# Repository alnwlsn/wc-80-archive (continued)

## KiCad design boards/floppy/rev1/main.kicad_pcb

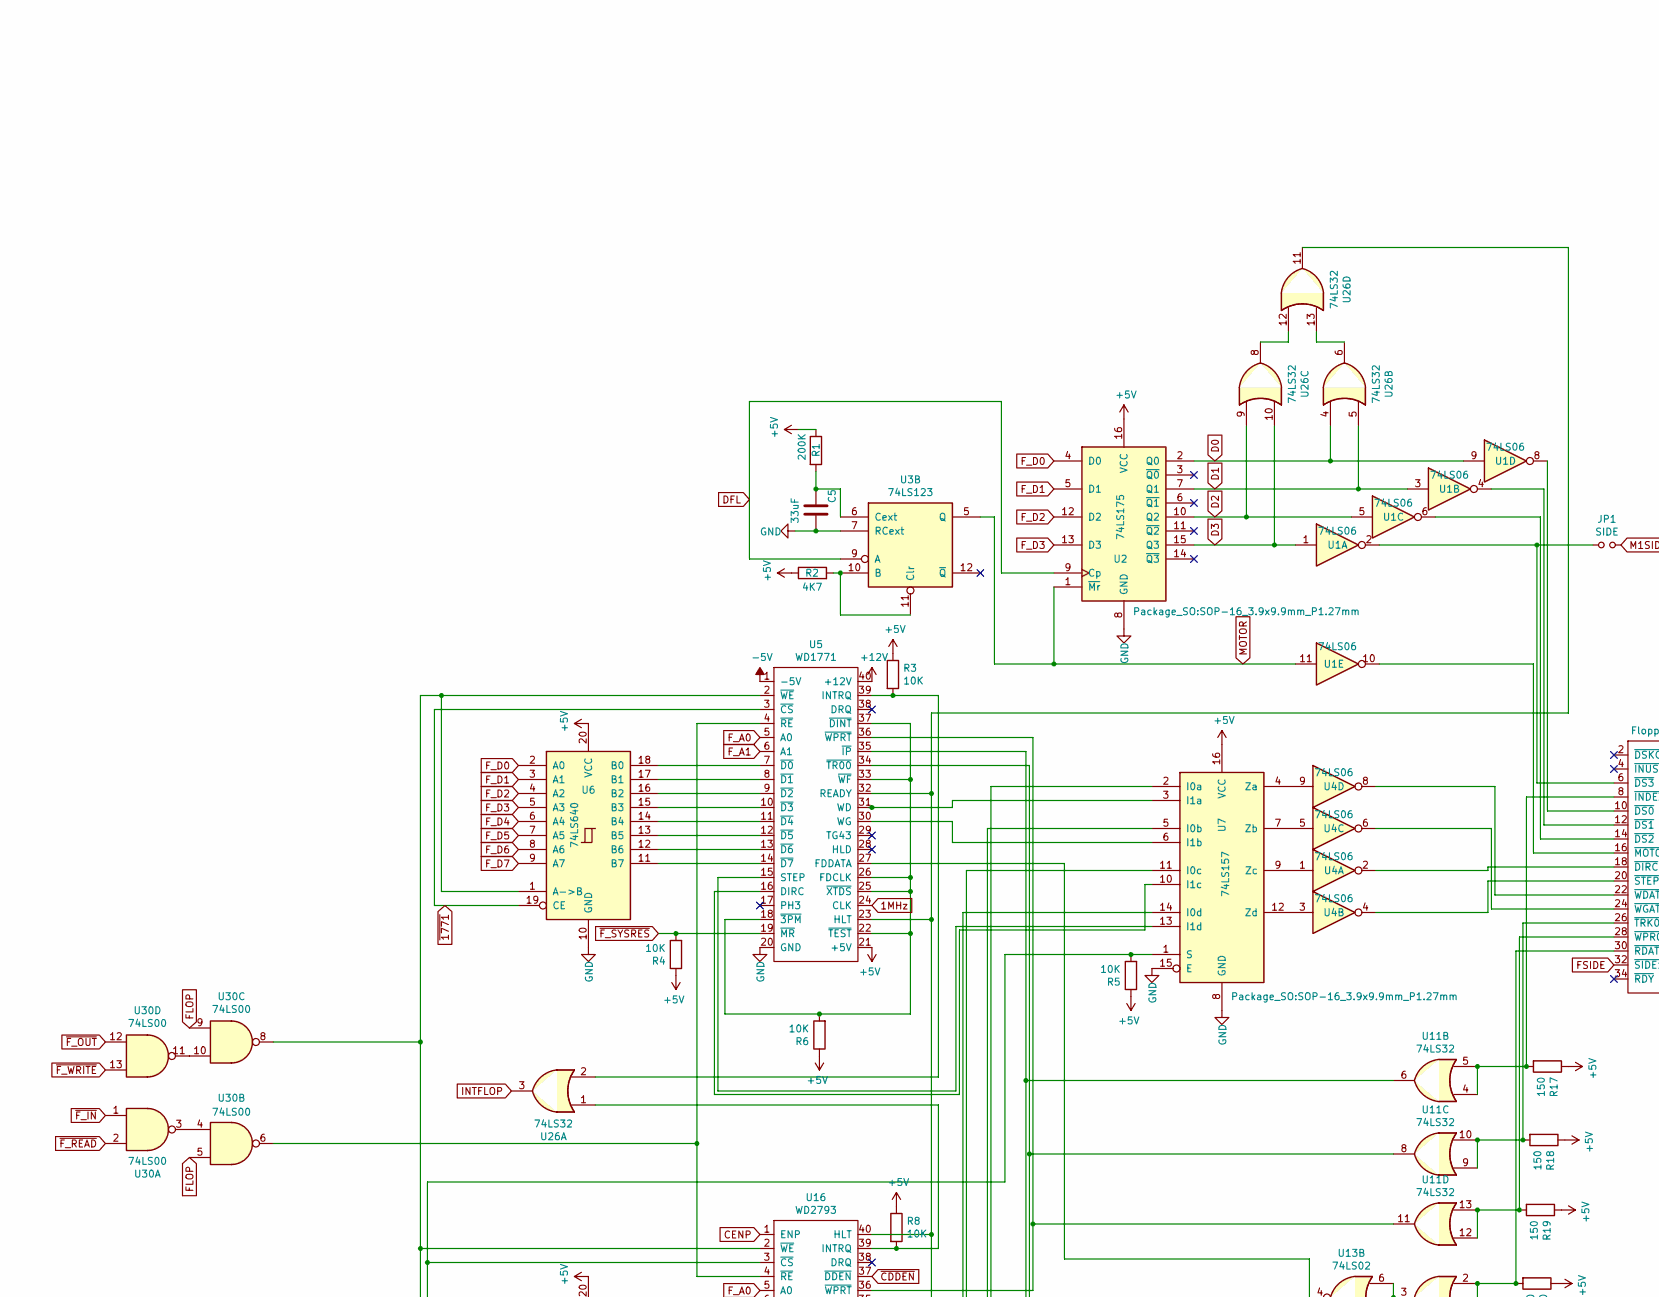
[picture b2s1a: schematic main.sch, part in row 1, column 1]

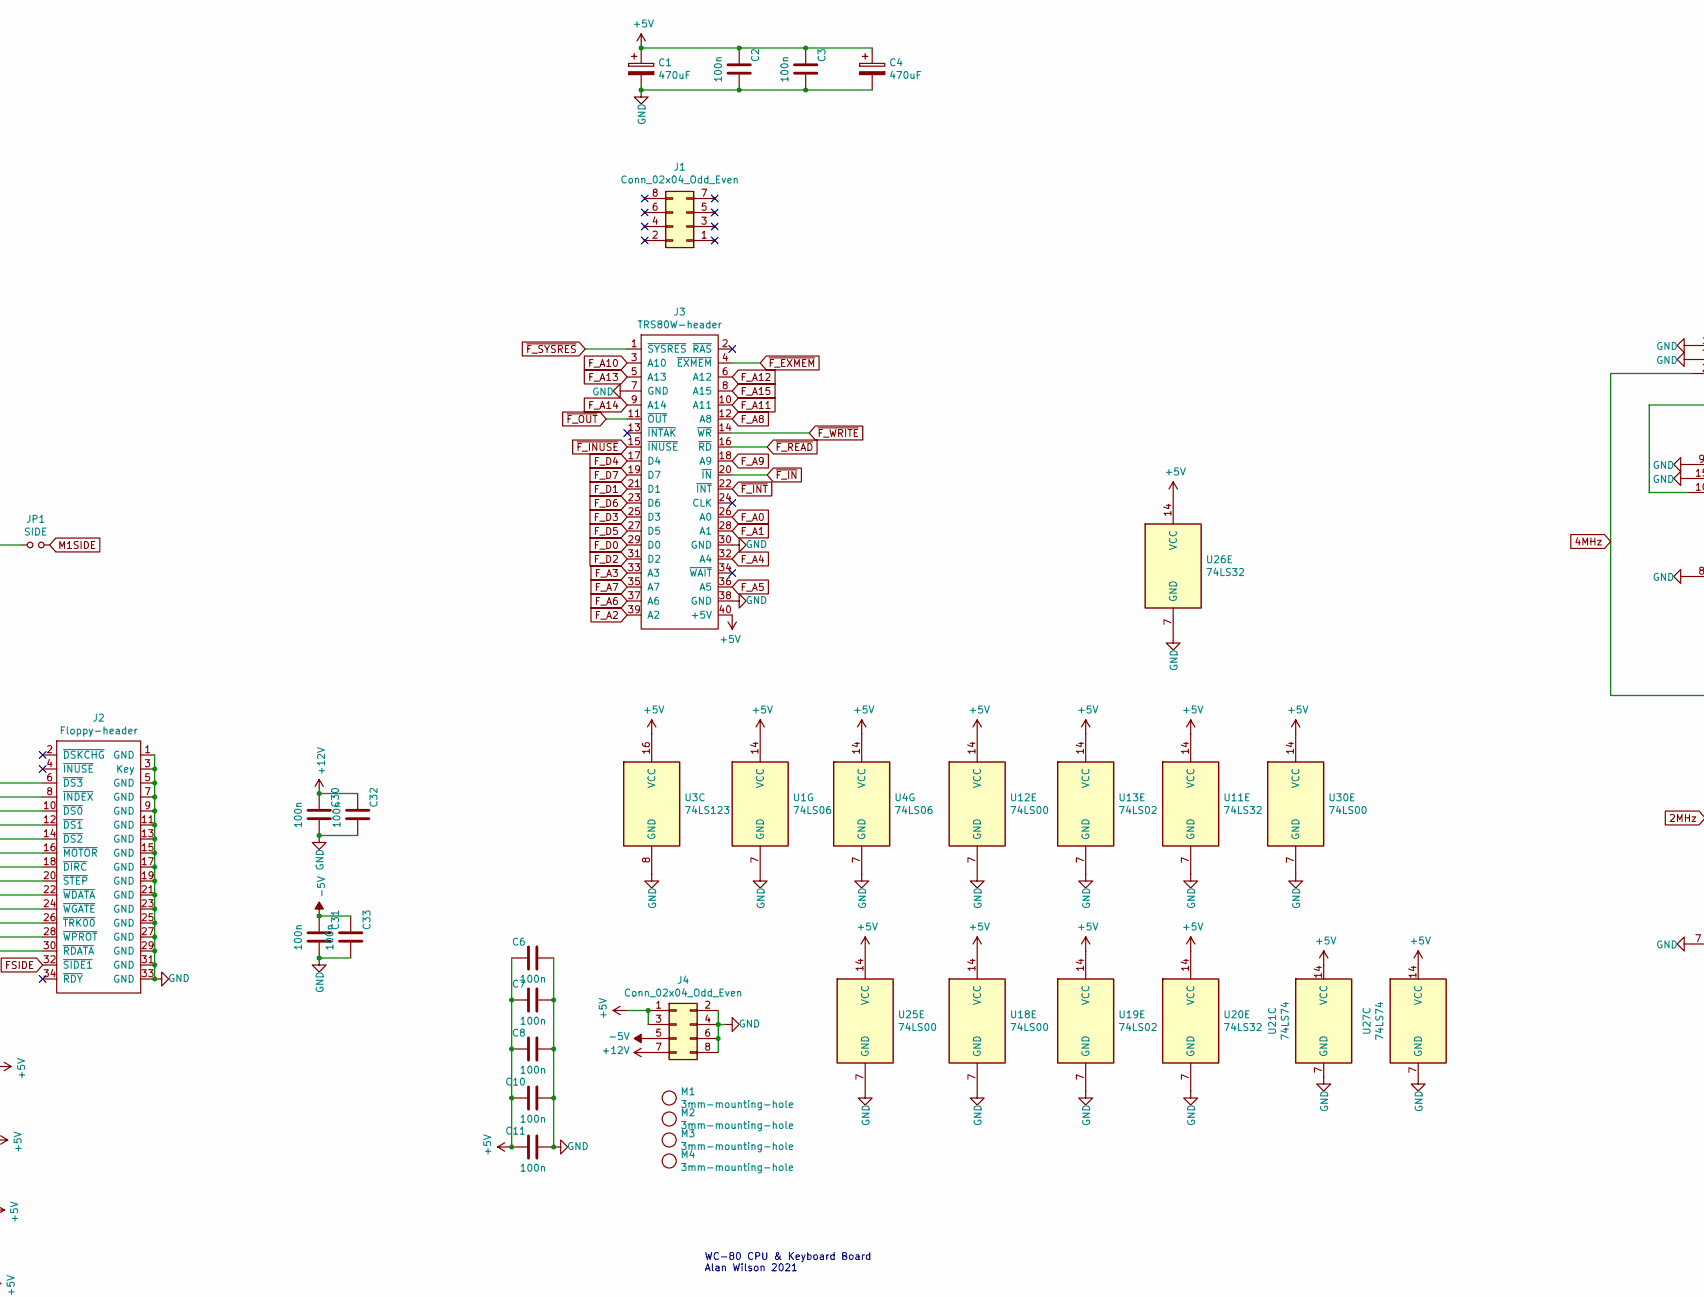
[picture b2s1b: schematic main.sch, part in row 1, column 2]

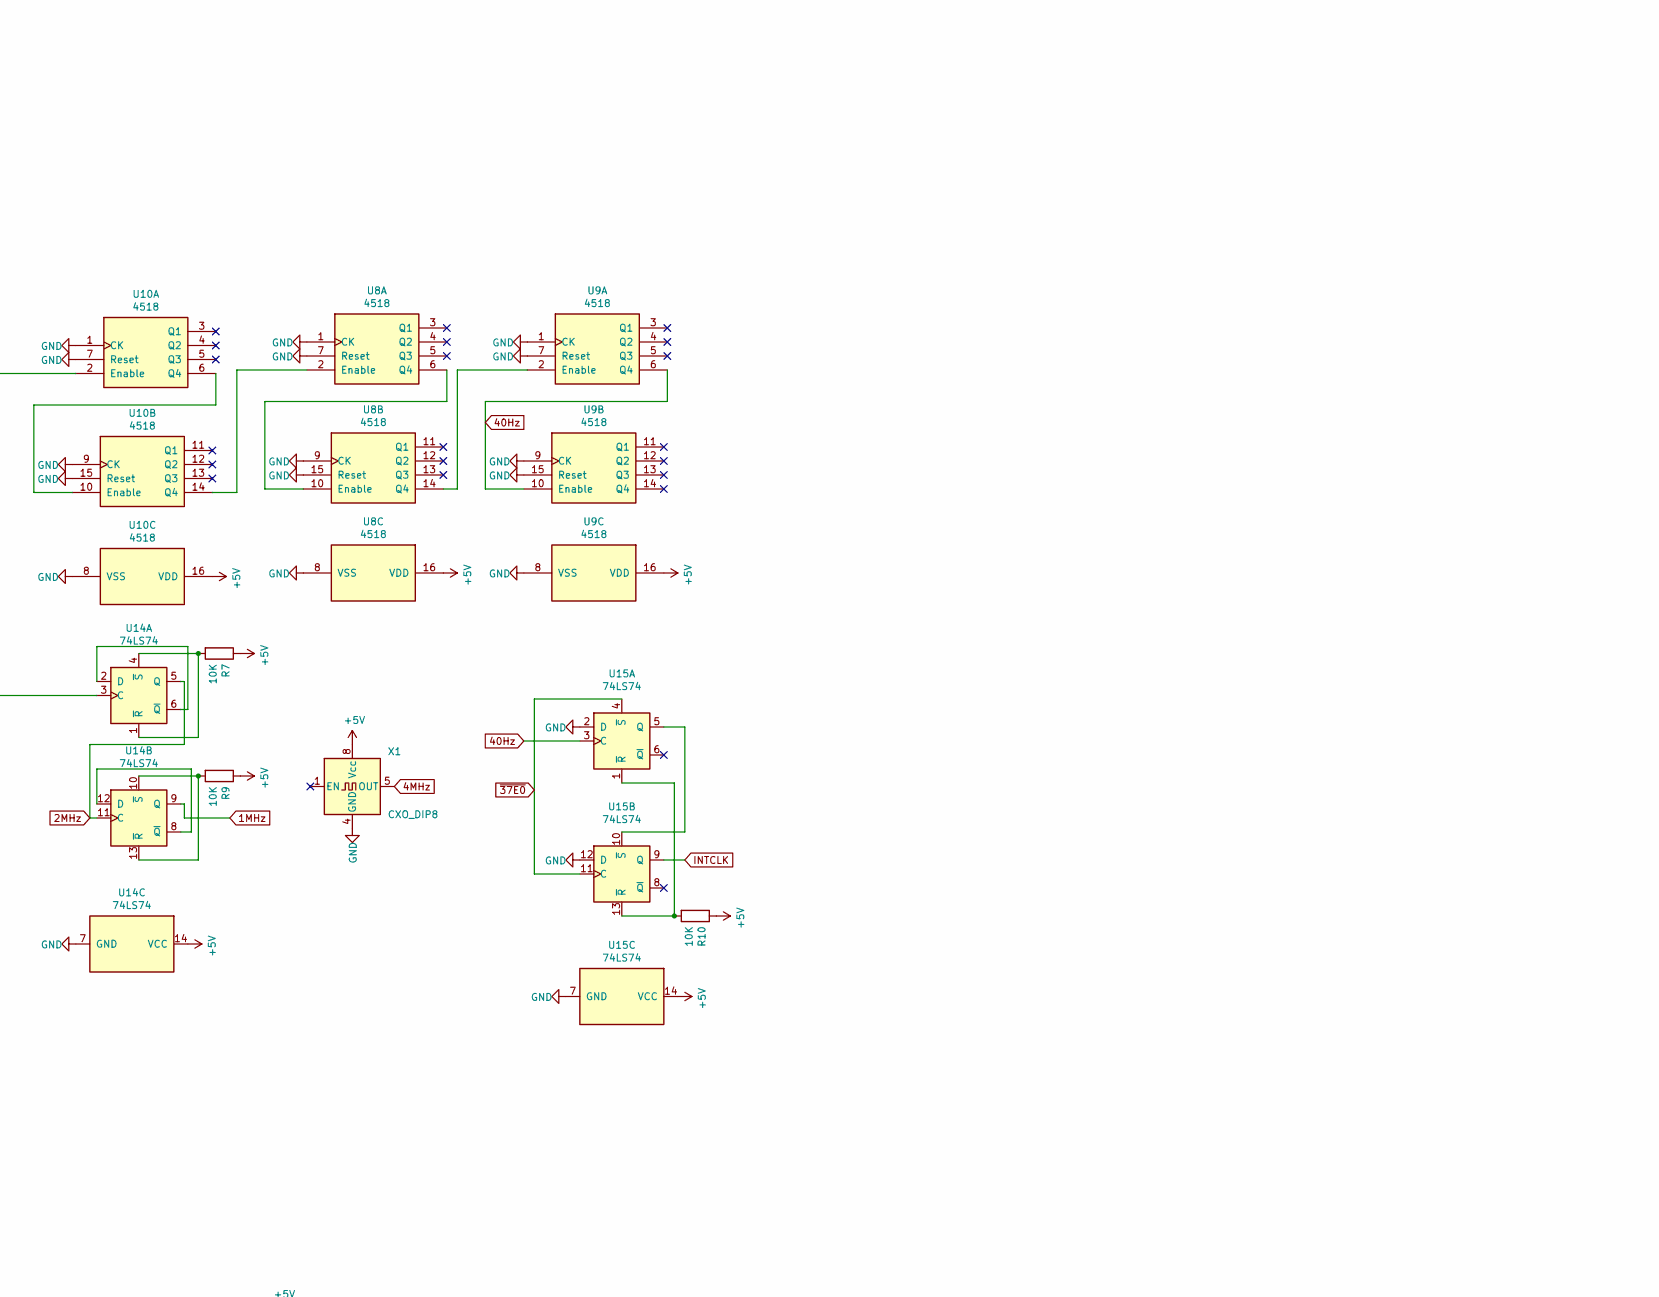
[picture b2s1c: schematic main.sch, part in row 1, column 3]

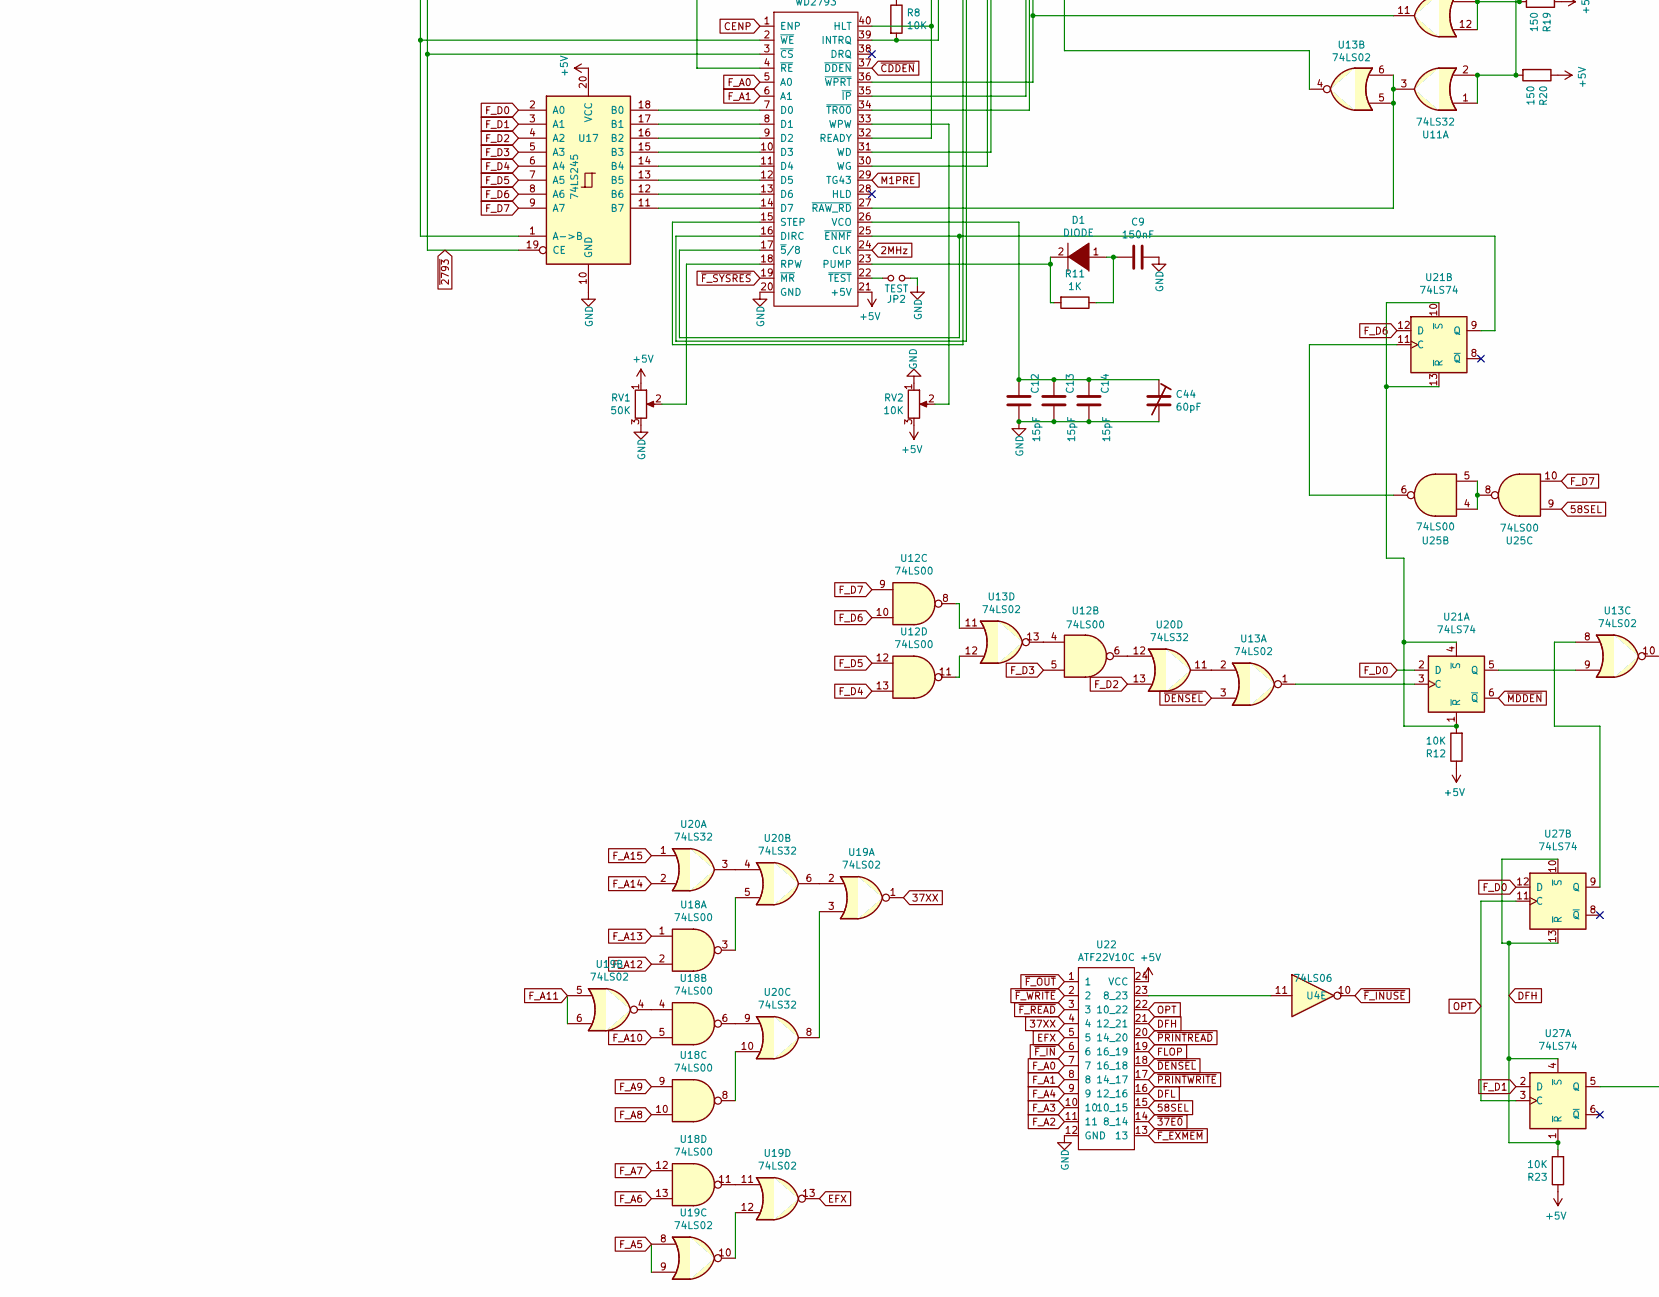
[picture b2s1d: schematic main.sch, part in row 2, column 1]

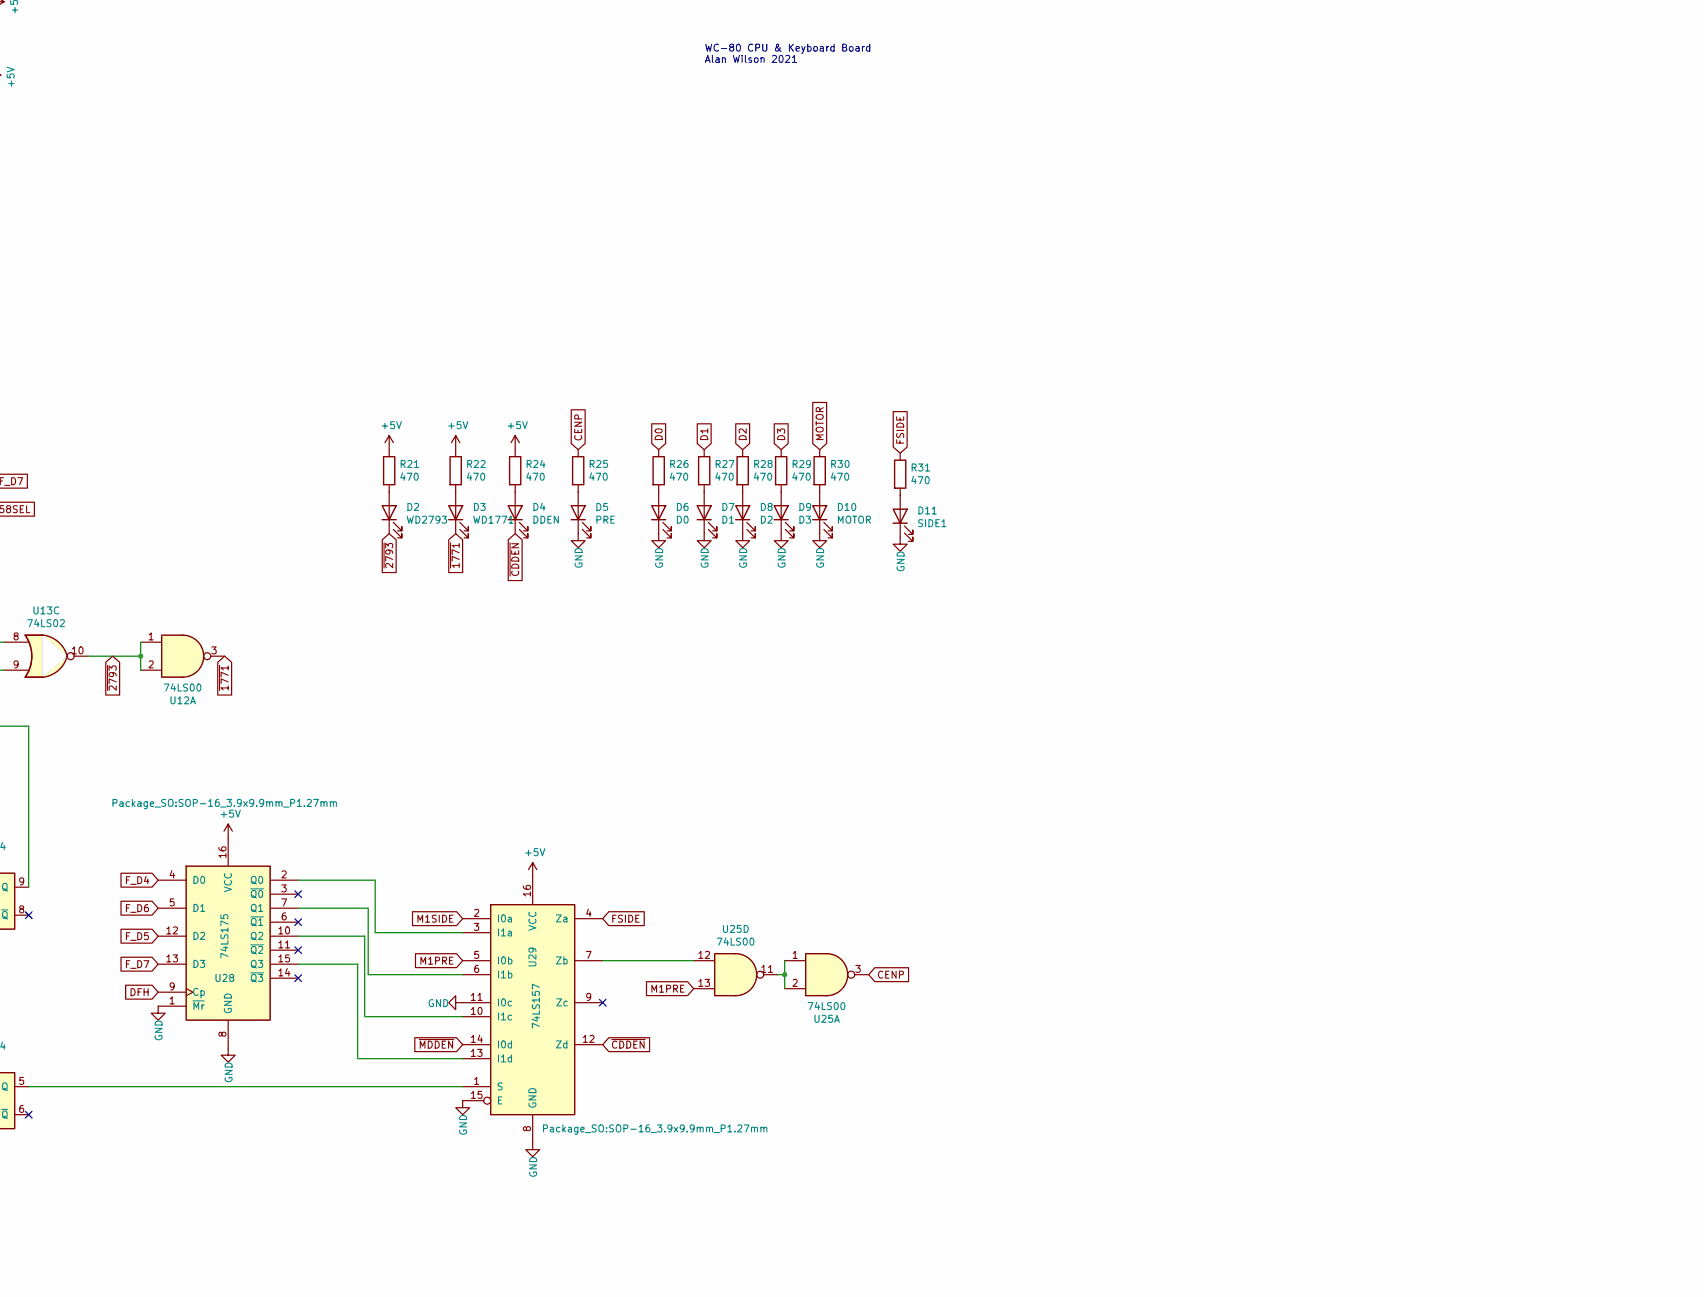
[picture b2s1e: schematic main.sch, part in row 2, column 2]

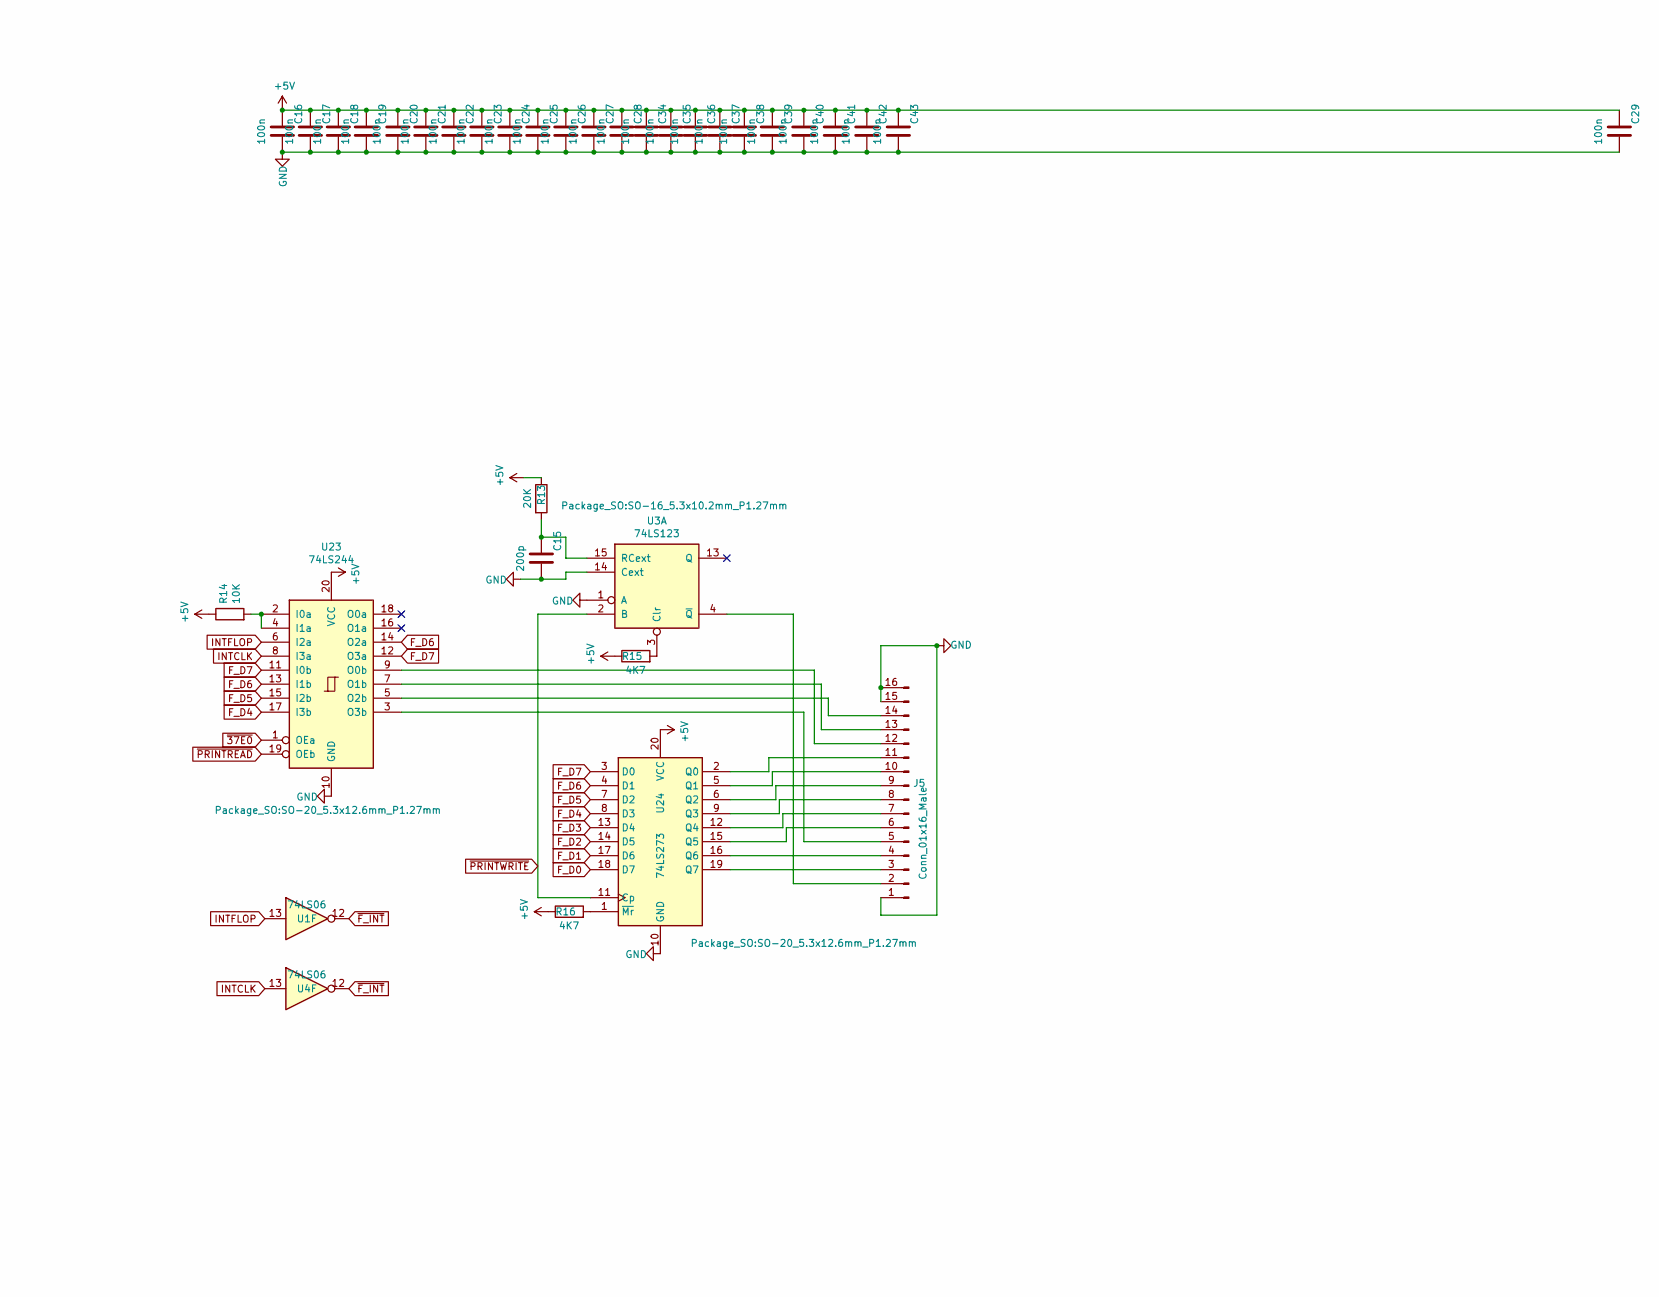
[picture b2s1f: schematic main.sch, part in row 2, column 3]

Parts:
C1, C4: 470uF; CP_Radial_D8.0mm_P3.50mm
C2, C3, C6, C7, C8, C10, C11, C16, C17, C18, C19, C20, C21, C22, C23, C24, C25, C26, C27, C28, C29, C30, C31, C32, C33, C34, C35, C36, C37, C38, C39, C40, C41, C42, C43: 100n; C_0805_2012Metric
C5: 33uF; C_0805_2012Metric
C9: 150nF; C_0805_2012Metric
C12, C13, C14: 15pF; C_0805_2012Metric
C15: 200p; C_0805_2012Metric
C44: 60pF; C_Rect_L7.0mm_W6.0mm_P5.00mm
D1: DIODE; D_0805_2012Metric
D2: WD2793; LED_D3.0mm
D3: WD1771; LED_D3.0mm
D4: DDEN; LED_D3.0mm
D5: PRE; LED_D3.0mm
D6: D0; LED_D3.0mm
D7: D1; LED_D3.0mm
D8: D2; LED_D3.0mm
D9: D3; LED_D3.0mm
D10: MOTOR; LED_D3.0mm
D11: SIDE1; LED_D3.0mm
J1, J4: Conn_02x04_Odd_Even; PinHeader_2x04_P2.54mm_Vertical
J2: Floppy-header; PinHeader_2x17_P2.54mm_Vertical
J3: TRS80W-header; PinHeader_2x20_P2.54mm_Vertical
J5: Conn_01x16_Male; PinHeader_2x08_P2.54mm_Vertical
JP1: SIDE; PinHeader_1x02_P2.54mm_Vertical
JP2: TEST; PinHeader_1x02_P2.54mm_Vertical
M1, M2, M3, M4: 3mm-mounting-hole; MountingHole_3.2mm_M3_DIN965
R1: 200K; R_0805_2012Metric
R2, R15, R16: 4K7; R_0805_2012Metric
R3, R4, R5, R6, R7, R8, R9, R10, R12, R14, R23: 10K; R_0805_2012Metric
R11: 1K; R_0805_2012Metric
R13: 20K; R_0805_2012Metric
R17, R18, R19, R20: 150; R_0805_2012Metric
R21, R22, R24, R25, R26, R27, R28, R29, R30, R31: 470; R_0805_2012Metric
RV1: 50K; Potentiometer_Bourns_3266W_Vertical
RV2: 10K; Potentiometer_Bourns_3266W_Vertical
U1, U4: 74LS06; SOIC-14_3.9x8.7mm_P1.27mm; Mouser 595-SN74LS06D
U2, U28: 74LS175; SOP-16_3.9x9.9mm_P1.27mm; Mouser 595-CD74HCT175M
U3: 74LS123; SO-16_5.3x10.2mm_P1.27mm; Mouser 595-SN74LS123NSR
U5: WD1771; DIP-40_W15.24mm_Socket
U6: 74LS640; SO-20_5.3x12.6mm_P1.27mm; Mouser 595-SN74LS640NSR
U7, U29: 74LS157; SOP-16_3.9x9.9mm_P1.27mm; Mouser 595-SN74HCT157D
U8, U9, U10: 4518; SOP-16_3.9x9.9mm_P1.27mm; Mouser 595-CD4518BM
U11, U20, U26: 74LS32; SOIC-14_3.9x8.7mm_P1.27mm; Mouser 595-SN74HCT32D
U12, U18, U25, U30: 74LS00; SOIC-14_3.9x8.7mm_P1.27mm; Mouser 595-SN74HCT00DE4
U13, U19: 74LS02; SOIC-14_3.9x8.7mm_P1.27mm; Mouser 595-SN74HCT02DR
U14, U15, U21, U27: 74LS74; SOIC-14_3.9x8.7mm_P1.27mm; Mouser 863-MC74HCT74ADR2G
U16: WD2793; DIP-40_W15.24mm_Socket
U17: 74LS245; SO-20_5.3x12.6mm_P1.27mm; Mouser 595-SN74LS245NS
U22: ATF22V10C; DIP-24_W7.62mm_Socket
U23: 74LS244; SO-20_5.3x12.6mm_P1.27mm; Mouser 595-SN74HCT244NSR
U24: 74LS273; SO-20_5.3x12.6mm_P1.27mm; Mouser 595-SN74LS273NSR
X1: CXO_DIP8; Oscillator_DIP-8; Mouser 815-ACH-4-EK

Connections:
1MHz: U5.24 (CLK), U14.9 (Q)
2MHz: U14.5 (Q), U14.11 (C), U16.24 (CLK)
4MHz: U10.2 (Enable), U14.3 (C), X1.5 (OUT)
37XX: U19.1, U22.4
40Hz: U9.6 (Q4), U9.10 (Enable), U15.3 (C)
58SEL: U22.15 (10_15), U25.9
+5V: C1.1, C2.1, C3.1, C4.1, C6.1, C7.1, C8.1, C10.1, C11.1, C16.1, C17.1, C18.1, C19.1, C20.1, C21.1, C22.1, C23.1, C24.1, C25.1, C26.1, C27.1, C28.1, C29.1, C34.1, C35.1, C36.1, C37.1, C38.1, C39.1, C40.1, C41.1, C42.1, C43.1, J3.40 (+5V), J4.1, J4.3, R1.1, R2.1, R3.1, R4.1, R5.1, R6.1, R7.1, R8.1, R9.1, R10.1, R12.1, R13.1, R14.1, R15.1, R16.1, R17.1, R18.1, R19.1, R20.1, R21.1, R22.1, R23.1, R24.1, RV1.1, RV2.3, U1.14 (VCC), U2.16 (VCC), U3.16 (VCC), U4.14 (VCC), U5.21 (+5V), U6.20 (VCC), U7.16 (VCC), U8.16 (VDD), U9.16 (VDD), U10.16 (VDD), U11.14 (VCC), U12.14 (VCC), U13.14 (VCC), U14.14 (VCC), U15.14 (VCC), U16.21 (+5V), U17.20 (VCC), U18.14 (VCC), U19.14 (VCC), U20.14 (VCC), U21.14 (VCC), U22.24 (VCC), U23.20 (VCC), U24.20 (VCC), U25.14 (VCC), U26.14 (VCC), U27.14 (VCC), U28.16 (VCC), U29.16 (VCC), U30.14 (VCC), X1.8 (Vcc)
+12V: C30.1, C32.1, J4.7, U5.40 (+12V)
-5V: C31.1, C33.1, J4.5, U5.1 (-5V)
CENP: R25.1, U16.1 (ENP), U25.3
D0: R26.1, U1.9, U2.2 (Q0), U26.4
D1: R27.1, U1.3, U2.7 (Q1), U26.5
D2: R28.1, U1.5, U2.10 (Q2), U26.9
D3: R29.1, U1.1, U2.15 (Q3), U26.10
DFH: R23.2, U22.21 (12_21), U27.1 (~R), U27.4 (~S), U27.10 (~S), U27.13 (~R), U28.9 (Cp)
DFL: U2.9 (Cp), U3.9 (A), U22.16 (12_16)
EFX: U19.13, U22.5
FLOP: U22.19 (16_19), U30.5, U30.9
FSIDE: J2.32 (~SIDE1~), R31.1, U29.4 (Za)
F_A0: J3.26 (A0), U5.5 (A0), U16.5 (A0), U22.7
F_A1: J3.28 (A1), U5.6 (A1), U16.6 (A1), U22.8
F_A2: J3.39 (A2), U22.11
F_A3: J3.33 (A3), U22.10
F_A4: J3.32 (A4), U22.9
F_A5: J3.36 (A5), U19.8, U19.9
F_A6: J3.37 (A6), U18.13
F_A7: J3.35 (A7), U18.12
F_A8: J3.12 (A8), U18.10
F_A9: J3.18 (A9), U18.9
F_A10: J3.3 (A10), U18.5
F_A11: J3.10 (A11), U19.5, U19.6
F_A12: J3.6 (A12), U18.2
F_A13: J3.5 (A13), U18.1
F_A14: J3.9 (A14), U20.2
F_A15: J3.8 (A15), U20.1
F_D0: J3.29 (D0), U2.4 (D0), U6.2 (A0), U17.2 (A0), U21.2 (D), U24.18 (D7), U27.12 (D)
F_D1: J3.21 (D1), U2.5 (D1), U6.3 (A1), U17.3 (A1), U24.17 (D6), U27.2 (D)
F_D2: J3.31 (D2), U2.12 (D2), U6.4 (A2), U17.4 (A2), U20.13, U24.14 (D5)
F_D3: J3.25 (D3), U2.13 (D3), U6.5 (A3), U12.5, U17.5 (A3), U24.13 (D4)
F_D4: J3.17 (D4), U6.6 (A4), U12.13, U17.6 (A4), U23.17 (I3b), U24.8 (D3), U28.4 (D0)
F_D5: J3.27 (D5), U6.7 (A5), U12.12, U17.7 (A5), U23.15 (I2b), U24.7 (D2), U28.12 (D2)
F_D6: J3.23 (D6), U6.8 (A6), U12.10, U17.8 (A6), U21.12 (D), U23.13 (I1b), U23.14 (O2a), U24.4 (D1), U28.5 (D1)
F_D7: J3.19 (D7), U6.9 (A7), U12.9, U17.9 (A7), U23.11 (I0b), U23.12 (O3a), U24.3 (D0), U25.10, U28.13 (D3)
GND: C1.2, C2.2, C3.2, C4.2, C5.2, C6.2, C7.2, C8.2, C9.1, C10.2, C11.2, C12.1, C13.1, C14.1, C15.2, C16.2, C17.2, C18.2, C19.2, C20.2, C21.2, C22.2, C23.2, C24.2, C25.2, C26.2, C27.2, C28.2, C29.2, C30.2, C31.2, C32.2, C33.2, C34.2, C35.2, C36.2, C37.2, C38.2, C39.2, C40.2, C41.2, C42.2, C43.2, C44.2, D5.1 (K), D6.1 (K), D7.1 (K), D8.1 (K), D9.1 (K), D10.1 (K), D11.1 (K), J2.1 (GND), J2.3 (Key), J2.5 (GND), J2.7 (GND), J2.9 (GND), J2.11 (GND), J2.13 (GND), J2.15 (GND), J2.17 (GND), J2.19 (GND), J2.21 (GND), J2.23 (GND), J2.25 (GND), J2.27 (GND), J2.29 (GND), J2.31 (GND), J2.33 (GND), J3.7 (GND), J3.30 (GND), J3.38 (GND), J4.2, J4.4, J4.6, J4.8, J5.1, J5.15, J5.16, JP2.2, RV1.3, RV2.1, U1.7 (GND), U2.8 (GND), U3.1 (A), U3.7 (RCext), U3.8 (GND), U3.14 (Cext), U4.7 (GND), U5.20 (GND), U6.10 (GND), U7.8 (GND), U7.15 (E), U8.1 (CK), U8.7 (Reset), U8.8 (VSS), U8.9 (CK), U8.15 (Reset), U9.1 (CK), U9.7 (Reset), U9.8 (VSS), U9.9 (CK), U9.15 (Reset), U10.1 (CK), U10.7 (Reset), U10.8 (VSS), U10.9 (CK), U10.15 (Reset), U11.7 (GND), U12.7 (GND), U13.7 (GND), U14.7 (GND), U15.2 (D), U15.7 (GND), U15.12 (D), U16.20 (GND), U17.10 (GND), U18.7 (GND), U19.7 (GND), U20.7 (GND), U21.7 (GND), U22.12 (GND), U23.10 (GND), U24.10 (GND), U25.7 (GND), U26.7 (GND), U27.7 (GND), U28.1 (~Mr), U28.8 (GND), U29.8 (GND), U29.11 (I0c), U29.15 (E), U30.7 (GND), X1.4 (GND)
INTCLK: U4.13, U15.9 (Q), U23.8 (I3a)
INTFLOP: U1.13, U23.6 (I2a), U26.3
M1PRE: U16.29 (TG43), U25.13, U29.5 (I0b)
M1SIDE: JP1.2, U29.2 (I0a)
MOTOR: R30.1, U1.11, U2.1 (~Mr), U3.5 (Q)
unnamed: C5.1, R1.2, U3.6 (Cext)
unnamed: C9.2, D1.1 (K), R11.1
unnamed: C12.2, C13.2, C14.2, C44.1, U16.26 (VCO)
unnamed: C15.1, R13.2, U3.15 (RCext)
unnamed: D1.2 (A), R11.2, U16.23 (PUMP)
unnamed: D2.2 (A), R21.2
unnamed: D3.2 (A), R22.2
unnamed: D4.2 (A), R24.2
unnamed: D5.2 (A), R25.2
unnamed: D6.2 (A), R26.2
unnamed: D7.2 (A), R27.2
unnamed: D8.2 (A), R28.2
unnamed: D9.2 (A), R29.2
unnamed: D10.2 (A), R30.2
unnamed: D11.2 (A), R31.2
unnamed: J2.6 (~DS3~), JP1.1, U1.2
unnamed: J2.8 (~INDEX~), R17.2, U11.4, U11.5
unnamed: J2.10 (~DS0~), U1.8
unnamed: J2.12 (~DS1~), U1.4
unnamed: J2.14 (~DS2~), U1.6
unnamed: J2.16 (~MOTOR~), U1.10
unnamed: J2.18 (~DIRC~), U4.2
unnamed: J2.20 (~STEP~), U4.4
unnamed: J2.22 (~WDATA~), U4.8
unnamed: J2.24 (~WGATE~), U4.6
unnamed: J2.26 (~TRK00~), R18.2, U11.9, U11.10
unnamed: J2.28 (~WPROT~), R19.2, U11.12, U11.13
unnamed: J2.30 (~RDATA~), R20.2, U11.1, U11.2
unnamed: J5.2, U3.4 (~Q)
unnamed: J5.3, U24.19 (Q7)
unnamed: J5.4, U24.16 (Q6)
unnamed: J5.5, U23.3 (O3b)
unnamed: J5.6, U24.15 (Q5)
unnamed: J5.7, U24.12 (Q4)
unnamed: J5.8, U24.9 (Q3)
unnamed: J5.9, U24.6 (Q2)
unnamed: J5.10, U24.5 (Q1)
unnamed: J5.11, U24.2 (Q0)
unnamed: J5.12, U23.9 (O0b)
unnamed: J5.13, U23.7 (O1b)
unnamed: J5.14, U23.5 (O2b)
unnamed: JP2.1, U16.22 (~TEST~)
unnamed: R2.2, U3.10 (B), U3.11 (Clr)
unnamed: R3.2, U5.39 (INTRQ), U26.2
unnamed: R6.2, U5.18 (~3PM~), U5.22 (~TEST~), U5.25 (~XTDS~), U5.26 (FDCLK), U5.33 (~WF~), U5.37 (~DINT~)
unnamed: R7.2, U14.1 (~R), U14.4 (~S)
unnamed: R8.2, U16.39 (INTRQ), U26.1
unnamed: R9.2, U14.10 (~S), U14.13 (~R)
unnamed: R10.2, U15.1 (~R), U15.13 (~R)
unnamed: R12.2, U21.1 (~R), U21.4 (~S), U21.10 (~S), U21.13 (~R)
unnamed: R14.2, U23.2 (I0a), U23.4 (I1a)
unnamed: R15.2, U3.3 (Clr)
unnamed: R16.2, U24.1 (~Mr)
unnamed: RV1.2, U16.18 (RPW)
unnamed: RV2.2, U16.33 (WPW)
unnamed: U4.1, U7.9 (Zc)
unnamed: U4.3, U7.12 (Zd)
unnamed: U4.5, U7.7 (Zb)
unnamed: U4.9, U7.4 (Za)
unnamed: U5.7 (~D0~), U6.18 (B0)
unnamed: U5.8 (~D1~), U6.17 (B1)
unnamed: U5.9 (~D2~), U6.16 (B2)
unnamed: U5.10 (~D3~), U6.15 (B3)
unnamed: U5.11 (~D4~), U6.14 (B4)
unnamed: U5.12 (~D5~), U6.13 (B5)
unnamed: U5.13 (~D6~), U6.12 (B6)
unnamed: U5.14 (~D7~), U6.11 (B7)
unnamed: U5.15 (STEP), U7.13 (I1d)
unnamed: U5.16 (DIRC), U7.10 (I1c)
unnamed: U5.30 (WG), U7.6 (I1b)
unnamed: U5.31 (WD), U7.3 (I1a)
unnamed: U8.6 (Q4), U8.10 (Enable)
unnamed: U8.14 (Q4), U9.2 (Enable)
unnamed: U10.6 (Q4), U10.10 (Enable)
unnamed: U8.2 (Enable), U10.14 (Q4)
unnamed: U11.3, U13.5, U13.6, U16.27 (~RAW_RD~)
unnamed: U5.35 (~IP~), U11.6, U16.35 (~IP~)
unnamed: U5.34 (~TR00~), U11.8, U16.34 (~TR00~)
unnamed: U5.36 (~WPRT~), U11.11, U16.36 (~WPRT~)
unnamed: U12.4, U13.13
unnamed: U12.6, U20.12
unnamed: U12.8, U13.11
unnamed: U12.11, U13.12
unnamed: U13.1, U21.3 (C)
unnamed: U13.2, U20.11
unnamed: U5.27 (FDDATA), U13.4
unnamed: U13.8, U27.9 (Q)
unnamed: U13.9, U21.5 (Q)
unnamed: U14.2 (D), U14.6 (~Q)
unnamed: U14.8 (~Q), U14.12 (D)
unnamed: U15.5 (Q), U15.10 (~S)
unnamed: U5.2 (~WE~), U6.1 (A->B), U16.2 (~WE~), U17.1 (A->B), U30.8
unnamed: U5.4 (~RE~), U16.4 (~RE~), U30.6
unnamed: U16.7 (D0), U17.18 (B0)
unnamed: U16.8 (D1), U17.17 (B1)
unnamed: U16.9 (D2), U17.16 (B2)
unnamed: U16.10 (D3), U17.15 (B3)
unnamed: U16.11 (D4), U17.14 (B4)
unnamed: U16.12 (D5), U17.13 (B5)
unnamed: U16.13 (D6), U17.12 (B6)
unnamed: U16.14 (D7), U17.11 (B7)
unnamed: U7.14 (I0d), U16.15 (STEP)
unnamed: U7.11 (I0c), U16.16 (DIRC)
unnamed: U16.17 (~5~/8), U16.25 (~ENMF~), U21.9 (Q)
unnamed: U7.5 (I0b), U16.30 (WG)
unnamed: U7.2 (I0a), U16.31 (WD)
unnamed: U5.23 (HLT), U5.32 (READY), U16.32 (READY), U16.40 (HLT), U26.11
unnamed: U18.3, U20.5
unnamed: U18.4, U19.4
unnamed: U18.6, U20.9
unnamed: U18.8, U20.10
unnamed: U18.11, U19.11
unnamed: U19.2, U20.6
unnamed: U19.3, U20.8
unnamed: U19.10, U19.12
unnamed: U20.3, U20.4
unnamed: U21.11 (C), U25.6
unnamed: U4.11, U22.23 (8_23)
unnamed: U25.1, U25.2, U25.11
unnamed: U25.4, U25.5, U25.8
unnamed: U25.12, U29.7 (Zb)
unnamed: U26.8, U26.12
unnamed: U26.6, U26.13
unnamed: U27.5 (Q), U29.1 (S)
unnamed: U28.2 (Q0), U29.3 (I1a)
unnamed: U28.7 (Q1), U29.6 (I1b)
unnamed: U28.10 (Q2), U29.10 (I1c)
unnamed: U28.15 (Q3), U29.13 (I1d)
unnamed: U30.3, U30.4
unnamed: U30.10, U30.11
OPT: U22.22 (10_22), U27.3 (C), U27.11 (C)
~37E0~: U15.4 (~S), U15.11 (C), U22.14 (8_14), U23.1 (OEa)
~1771~: D3.1 (K), U5.3 (~CS~), U6.19 (CE), U12.3
~2793~: D2.1 (K), R5.2, U7.1 (S), U12.1, U12.2, U13.10, U16.3 (~CS~), U17.19 (CE)
~CDDEN~: D4.1 (K), U16.37 (~DDEN~), U29.12 (Zd)
~DENSEL~: U13.3, U22.18 (16_18)
~F_EXMEM~: J3.4 (~EXMEM~), U22.13
~F_INT~: J3.22 (~INT~), U1.12, U4.12
~F_INUSE~: J3.15 (~INUSE~), U4.10
~F_IN~: J3.20 (~IN~), U22.6, U30.1
~F_OUT~: J3.11 (~OUT~), U22.1, U30.12
~F_READ~: J3.16 (~RD~), U22.3, U30.2
~F_SYSRES~: J3.1 (~SYSRES~), R4.2, U5.19 (~MR~), U16.19 (~MR~)
~F_WRITE~: J3.14 (~WR~), U22.2, U30.13
~MDDEN~: U21.6 (~Q), U29.14 (I0d)
~PRINTREAD~: U22.20 (14_20), U23.19 (OEb)
~PRINTWRITE~: U3.2 (B), U22.17 (14_17), U24.11 (Cp)

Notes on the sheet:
WC-80 CPU & Keyboard Board Alan Wilson 2021
